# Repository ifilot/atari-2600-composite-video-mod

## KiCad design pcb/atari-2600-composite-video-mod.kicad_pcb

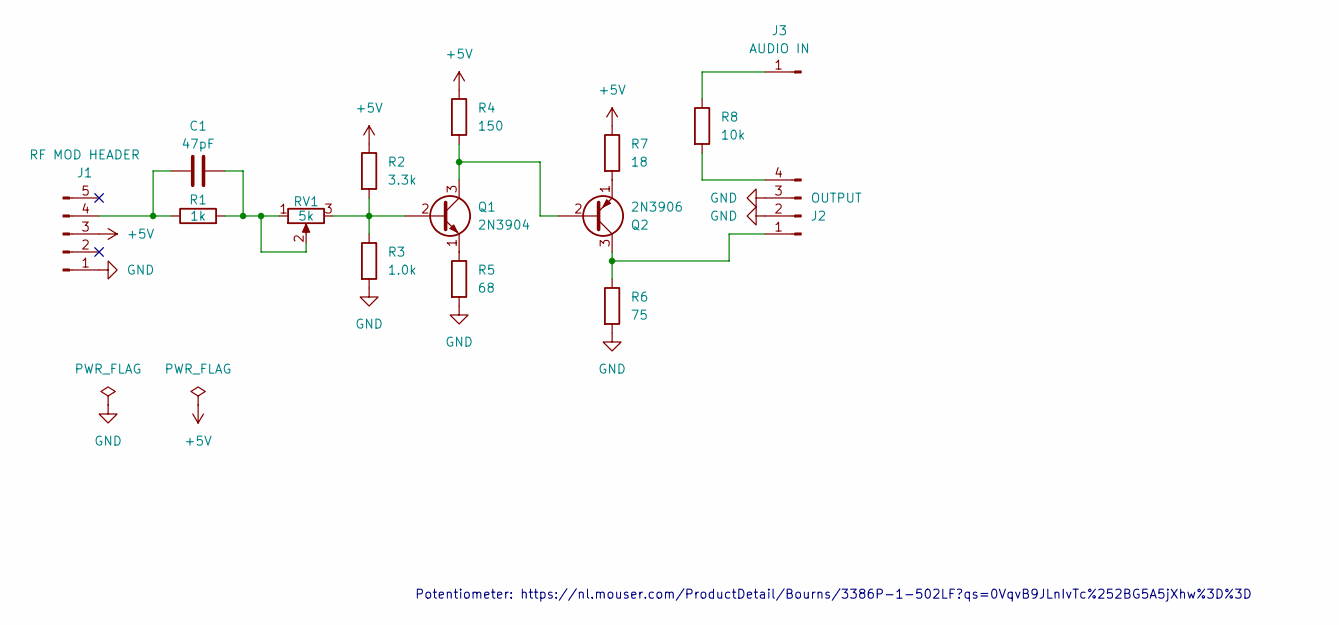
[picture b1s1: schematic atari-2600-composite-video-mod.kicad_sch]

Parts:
C1: 47pF; C_Disc_D5.0mm_W2.5mm_P5.00mm
J1: RF MOD HEADER; PinHeader_1x05_P2.54mm_Vertical
J2: OUTPUT; PinHeader_1x04_P2.54mm_Vertical
J3: AUDIO IN; PinHeader_1x01_P2.54mm_Vertical
Q1: 2N3904; TO-92_Inline
Q2: 2N3906; TO-92_Inline
R1: 1k; R_Axial_DIN0207_L6.3mm_D2.5mm_P7.62mm_Horizontal
R2: 3.3k; R_Axial_DIN0207_L6.3mm_D2.5mm_P7.62mm_Horizontal
R3: 1.0k; R_Axial_DIN0207_L6.3mm_D2.5mm_P7.62mm_Horizontal
R4: 150; R_Axial_DIN0207_L6.3mm_D2.5mm_P7.62mm_Horizontal
R5: 68; R_Axial_DIN0207_L6.3mm_D2.5mm_P7.62mm_Horizontal
R6: 75; R_Axial_DIN0207_L6.3mm_D2.5mm_P7.62mm_Horizontal
R7: 18; R_Axial_DIN0207_L6.3mm_D2.5mm_P7.62mm_Horizontal
R8: 10k; R_Axial_DIN0207_L6.3mm_D2.5mm_P7.62mm_Horizontal
RV1: 5k; Potentiometer_Bourns_3386P_Vertical

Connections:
+5V: J1.3, R2.1, R4.1, R7.1
GND: J1.1, J2.2, J2.3, R3.2, R5.2, R6.2
unnamed: C1.2, R1.2, RV1.1, RV1.2
unnamed: C1.1, J1.4, R1.1
unnamed: J2.1, Q2.3 (C), R6.1
unnamed: J2.4, R8.2
unnamed: J3.1, R8.1
unnamed: Q1.2 (B), R2.2, R3.1, RV1.3
unnamed: Q1.3 (C), Q2.2 (B), R4.2
unnamed: Q1.1 (E), R5.1
unnamed: Q2.1 (E), R7.2

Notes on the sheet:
Potentiometer: https://nl.mouser.com/ProductDetail/Bourns/3386P-1-502LF?qs=0VqvB9JLnIvTc%252BG5A5jXhw%3D%3D

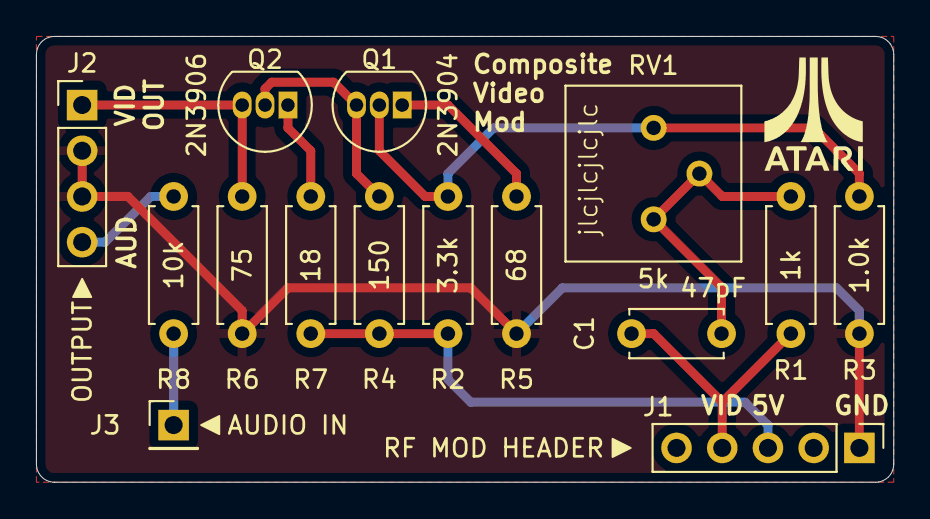
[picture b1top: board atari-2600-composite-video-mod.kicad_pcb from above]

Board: 2 copper layers, 47.6 x 24.8 mm, 15 parts (0 on the bottom side), 11 nets.

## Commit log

2025-02-06 Writing comments
